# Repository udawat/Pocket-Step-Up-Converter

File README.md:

Pocket-Boost-Converter
========================

The Pocket-Boost Converter is a DC-to-DC Step-Up Converter which generates a supply voltage of 5 V or 3.3 V from a single-cell AA alkaline battery.

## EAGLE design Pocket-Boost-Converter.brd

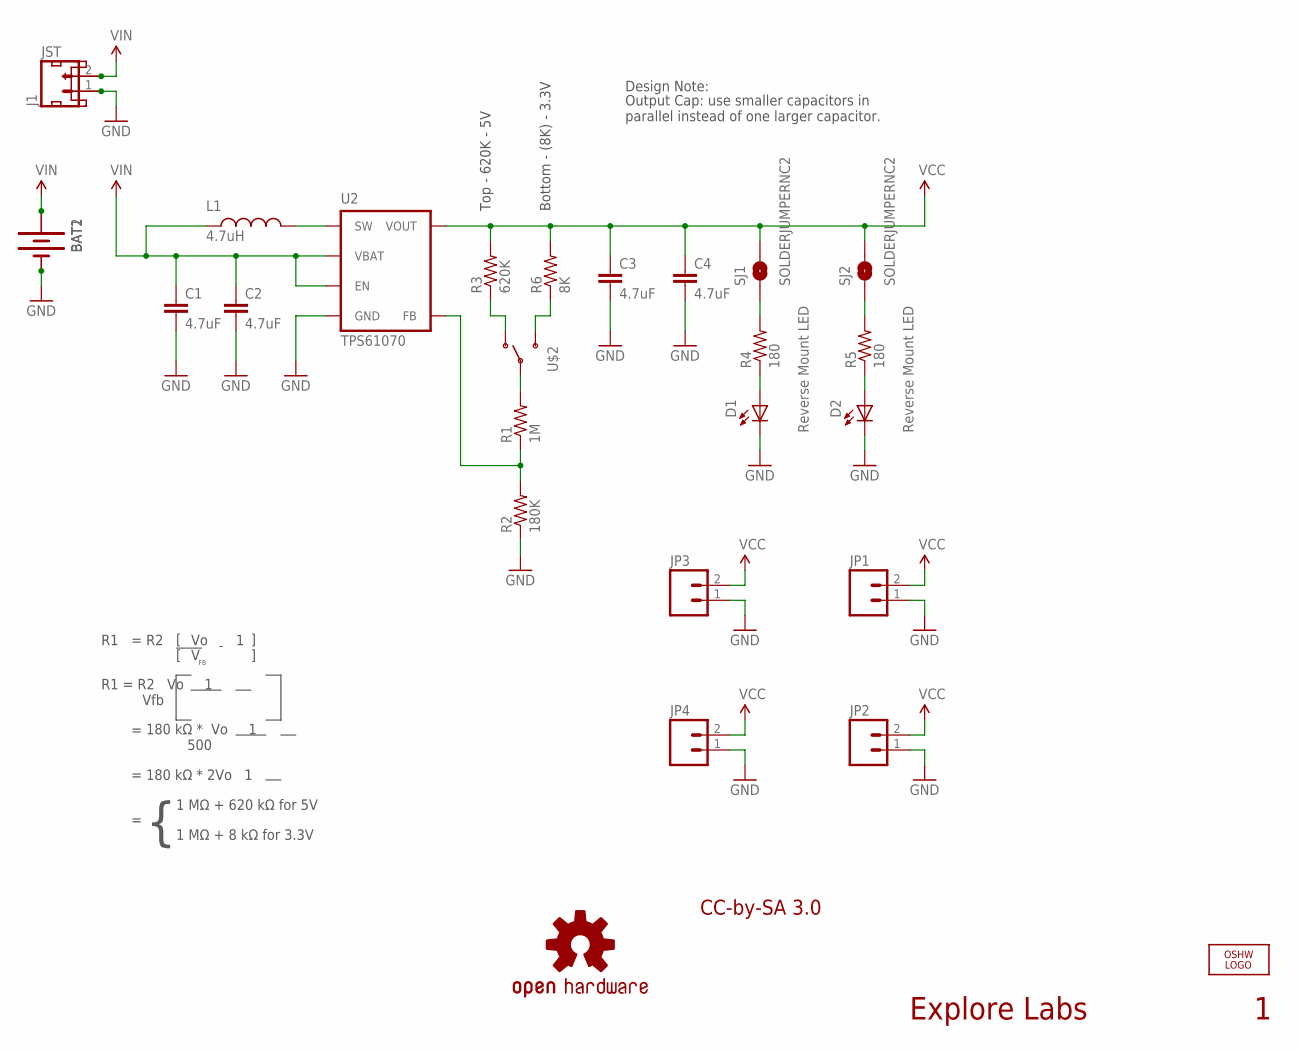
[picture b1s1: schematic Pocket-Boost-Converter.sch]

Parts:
BAT1: BATTERYONE-HOLE-REMOVED-FOR-REV-MNT-LED; BATTERY-AA-HOLDER-BBPS
BAT2: BATTERYNO-HOLES; BATTERY-2AA-HOLDER-BBPS
C1, C2, C3, C4: 4.7uF; 0603-CAP
D1, D2: Reverse Mount LED; LED-REV-MOUNT
J1: JST_2MM_MALE; JST-2-SMD
JP1, JP2, JP3, JP4: M02PTH; 1X02
JST: M02-JST-2-PTH-NO_SILK; JST-2-PTH-NS
L1: 4.7uH; INDUCTOR-MSS4020
LOGO1: OSHW_LOGO_FILLX0200-NT; OSHW_FILLX200_NOTEXT
LOGO2: OSHW-LOGOS; OSHW-LOGO-S
R1: 1M; 0603-RES
R2: 180K; 0603-RES
R3: 620K; 0603-RES
R4, R5: 180; 0603-RES
R6: 8K; 0603-RES
SJ1, SJ2: SOLDERJUMPERNC2; SJ_2S-NOTRACE
U2: TPS61070; DDC
U$2: SWITCH_SPDTSMD-NO-HOLES; SWITCH-SPST-SMD-A-FOR-BBPS

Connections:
GND: BAT1.GND (-), BAT2.GND (-), C1.2, C2.2, C3.2, C4.2, D1.CATHODE, D2.CATHODE, J1.1 (-), JP1.1, JP2.1, JP3.1, JP4.1, JST.1, R2.1, U2.2 (GND)
unnamed: R5.2, SJ2.1
unnamed: R3.1, U$2.A (A-OUT)
unnamed: R1.1, R2.2, U2.4 (FB)
unnamed: R1.2, U$2.B (BC-IN), U$2.C (BC-IN)
unnamed: D2.ANODE, R5.1
unnamed: R6.1, U$2.D (D-OUT)
unnamed: R4.2, SJ1.1
unnamed: D1.ANODE, R4.1
SW: L1.2, U2.1 (SW)
VBAT: BAT1.PWR (+), BAT2.PWR (+), C1.1, C2.1, J1.2 (+), JST.2, L1.1, U2.3 (EN), U2.6 (VBAT)
VOUT: C3.1, C4.1, JP1.2, JP2.2, JP3.2, JP4.2, R3.2, R6.2, SJ1.2, SJ2.2, U2.5 (VOUT)

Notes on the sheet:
Bottom - (8K) - 3.3V
Top - 620K - 5V
Output Cap: use smaller capacitors in parallel instead of one larger capacitor.
Explore Labs
[ [
____
] ]
R1 = R2 Vo 1 Vfb
180 kΩ * Vo 1 500
180 kΩ * 2Vo 1
1 MΩ + 620 kΩ for 5V
1 MΩ + 8 kΩ for 3.3V
Design Note:
CC-by-SA 3.0

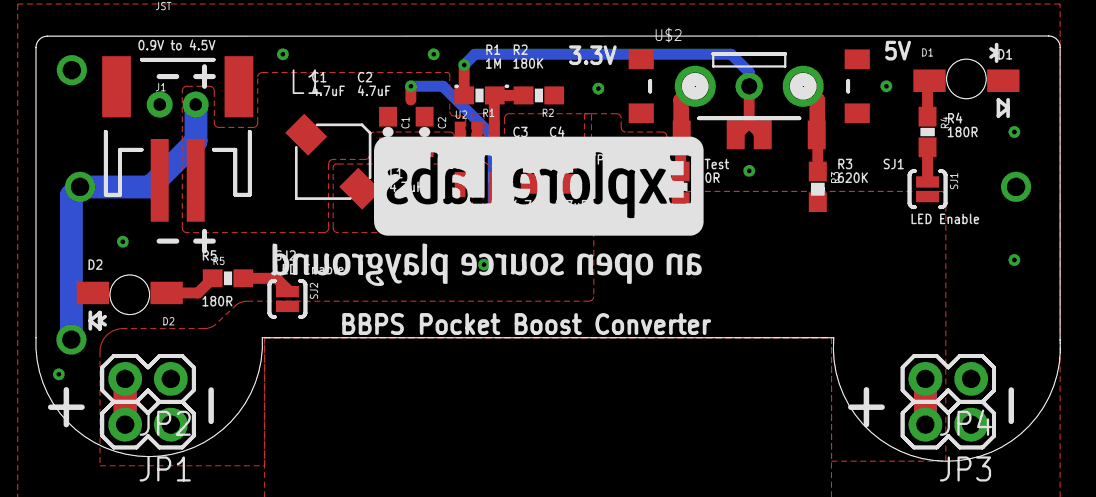
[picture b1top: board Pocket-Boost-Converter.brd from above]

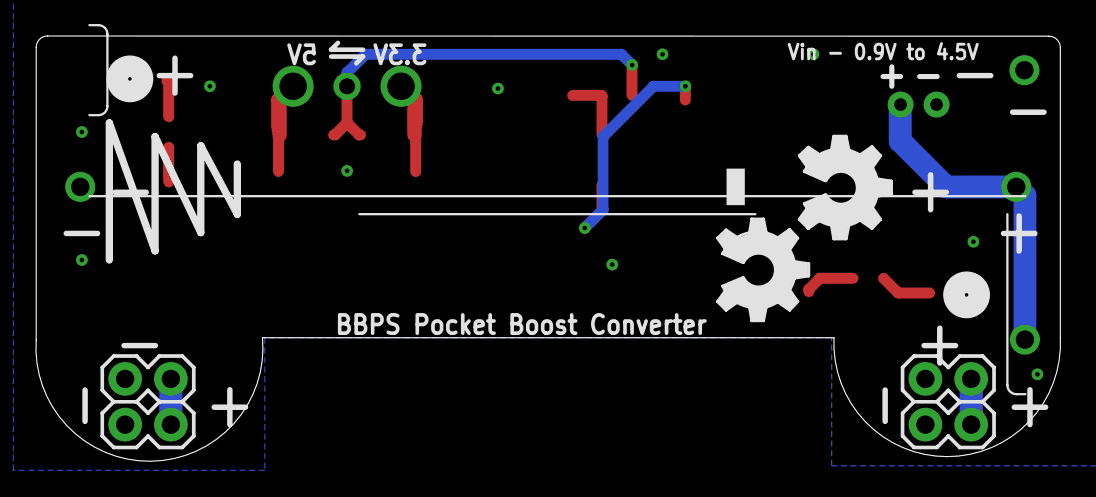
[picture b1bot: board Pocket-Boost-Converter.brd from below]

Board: 2 copper layers, 56.9 x 23.6 mm, 28 parts (4 on the bottom side), 12 nets.

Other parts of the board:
U$4: EXLABS_LOGO_0.5

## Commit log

2014-03-11 initial commit
    all EAGLE files with gerber
2014-03-11 ReadMe file update
2014-03-11 ReadMe again updated
2015-04-08 renamed

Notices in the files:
parts and their libraries:
SparkFun-Passives: Licensing: CC v3.0 Share-Alike You are welcome to use this library for commercial purposes.
